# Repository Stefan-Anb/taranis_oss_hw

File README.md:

# Taranis Pcb

BMS PCB for Taranis Project
Kicad files
PCB Layout is not finished yet. Schematics are proven from a proprietary project.

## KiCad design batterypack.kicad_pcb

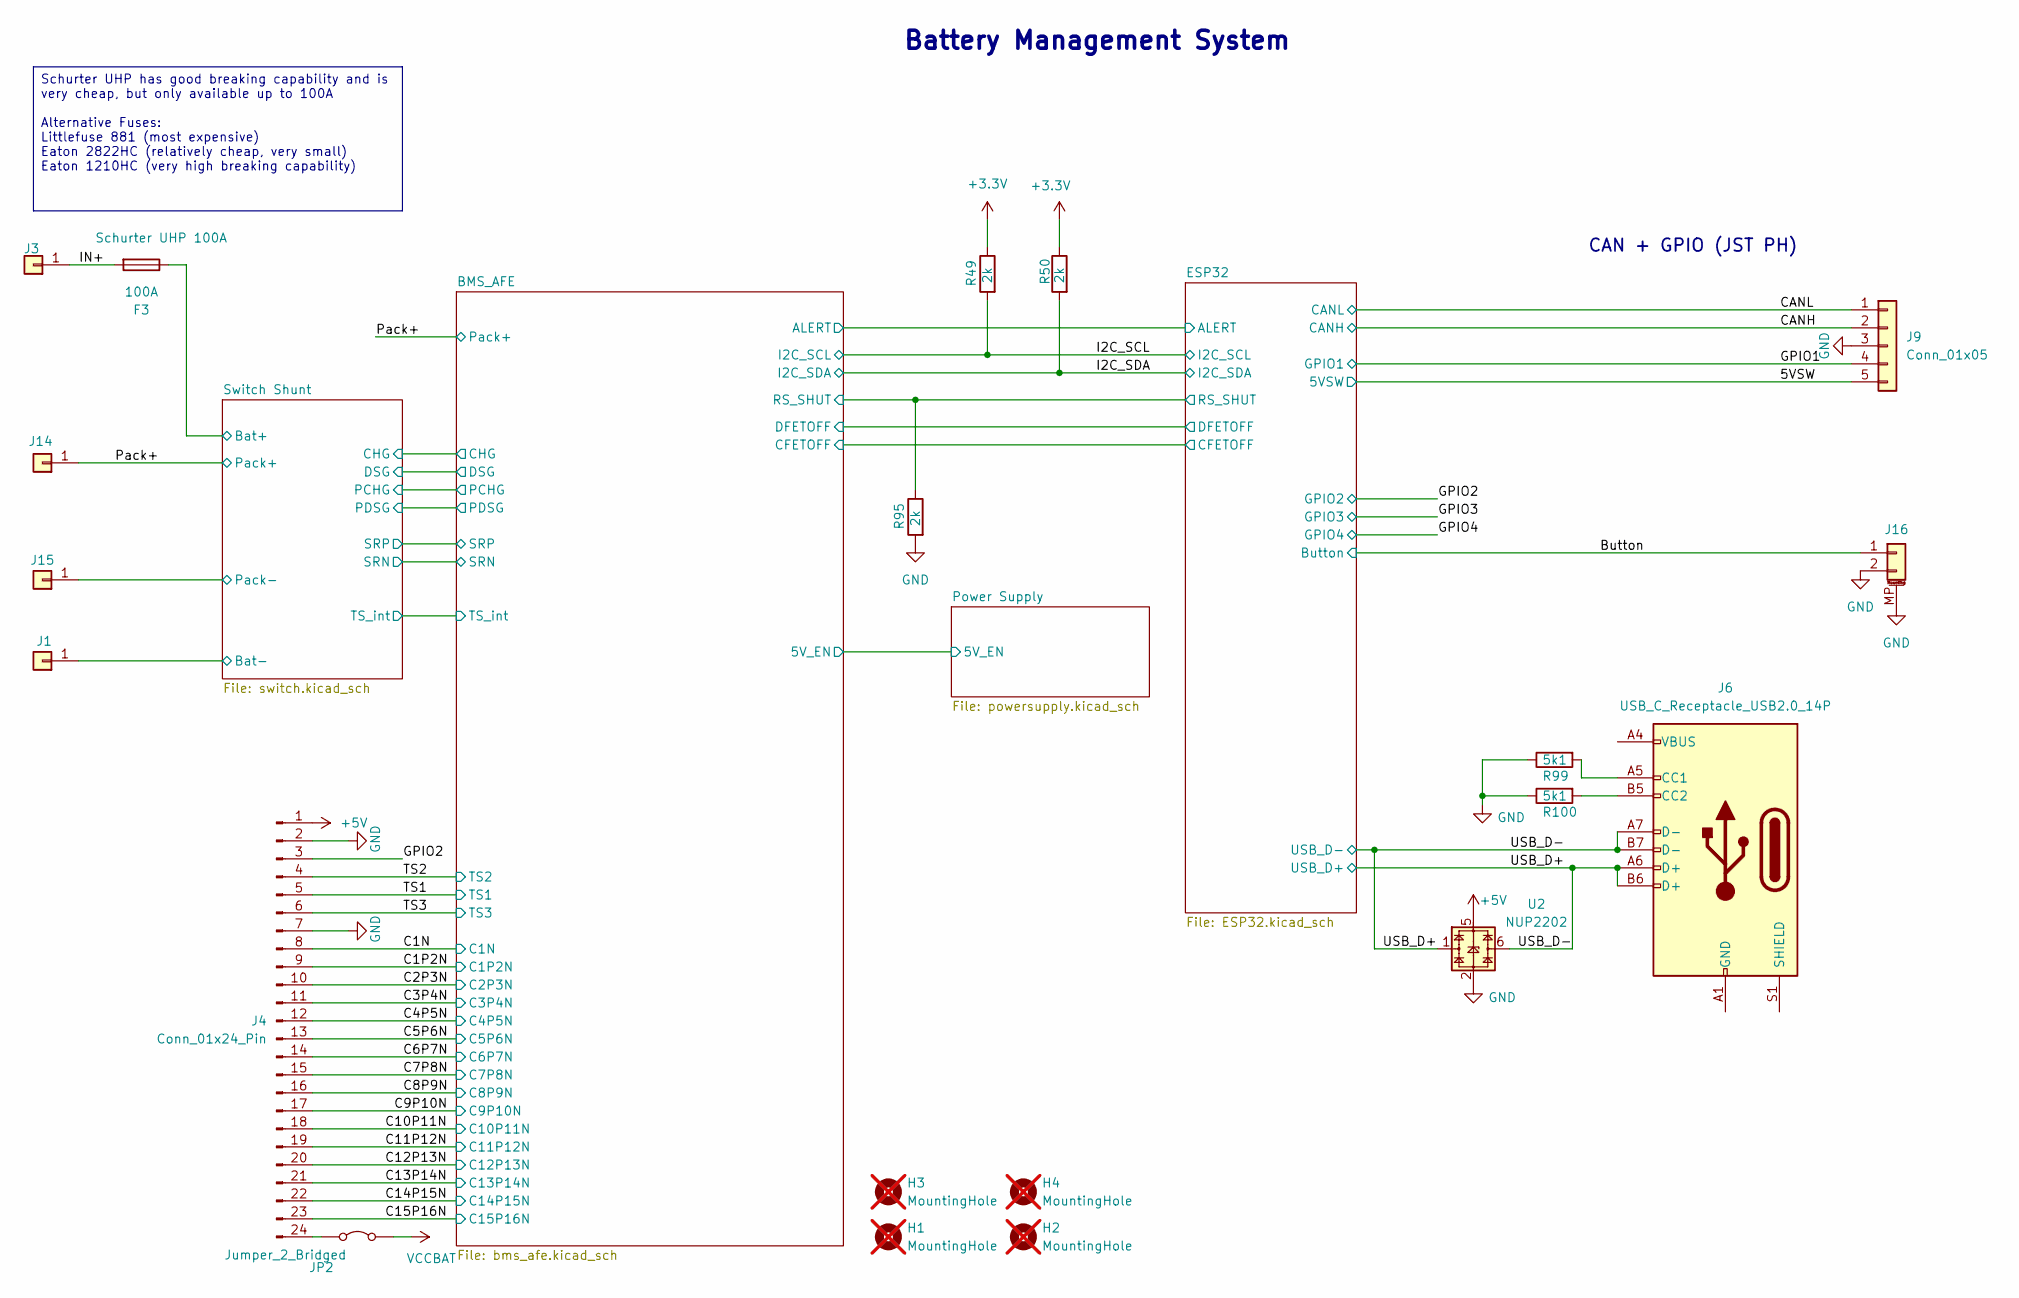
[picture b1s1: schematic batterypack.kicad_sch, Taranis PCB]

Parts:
F3: 100A; Shurter_UHP; MPN C20110673
H1, H2, H3, H4: MountingHole; MountingHole_3.2mm_M3; not fitted
J1, J3: Conn_01x01; Wuerth_REDCUBE-THR_WP-THRBU_74650094_THR; MPN C9900208421
J4: Conn_01x24_Pin
J6: USB_C_Receptacle_USB2.0_14P
J9: Conn_01x05
J14, J15: Conn_01x01; Wuerth_REDCUBE-THR_WP-THRBU_74650094_THR; MPN C25168763
J16: Conn_01x02; JST_PH_S2B-PH-K_1x02_P2.00mm_Horizontal; MPN C160352
JP2: Jumper_2_Bridged; SolderJumper-2_P1.3mm_Bridged_RoundedPad1.0x1.5mm
R49, R50, R95: 2k; R_0402_1005Metric; MPN C4109
R99, R100: 5k1; R_0402_1005Metric; MPN C25905
U2: NUP2202; SOT-363_SC-70-6; MPN C4355033

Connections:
+3.3V: R49.1, R50.1; also elsewhere on the board
+5V: J4.1, J4.5, U2.5; also elsewhere on the board
/BMS_AFE/RS_SHUT: R95.1; also elsewhere on the board
/Button: J16.1; also elsewhere on the board
/C1N: J4.12; also elsewhere on the board
/C1P2N: J4.13; also elsewhere on the board
/C2P3N: J4.14; also elsewhere on the board
/C3P4N: J4.15; also elsewhere on the board
/C4P5N: J4.16; also elsewhere on the board
/C5P6N: J4.17; also elsewhere on the board
/C6P7N: J4.18; also elsewhere on the board
/C7P8N: J4.19; also elsewhere on the board
/C8P9N: J4.20; also elsewhere on the board
/C9P10N: J4.21; also elsewhere on the board
/C10P11N: J4.22; also elsewhere on the board
/C11P12N: J4.23; also elsewhere on the board
/C13P14N: J4.25; also elsewhere on the board
/C14P15N: J4.26; also elsewhere on the board
/C15P16N: J4.27; also elsewhere on the board
/I2C_SCL: R49.2; also elsewhere on the board
/I2C_SDA: R50.2; also elsewhere on the board
/IN+: F3.2, J3.1
/Pack+: J14.1; also elsewhere on the board
/Switch Shunt/Bat+: F3.1; also elsewhere on the board
/Switch Shunt/Bat-: J1.1; also elsewhere on the board
/Switch Shunt/Pack-: J15.1; also elsewhere on the board
/TS1: J4.9; also elsewhere on the board
/TS2: J4.8; also elsewhere on the board
/TS3: J4.10; also elsewhere on the board
/USB_D+: J6.A6 (D+), J6.A7 (D-), J6.B6 (D+), J6.B7 (D-), U2.1, U2.6; also elsewhere on the board
unnamed: J6.A5 (CC1), R99.2
unnamed: J6.B5 (CC2), R100.2
unnamed: J6.A1 (GND), J6.A12 (GND), J6.B1 (GND), J6.B12 (GND)
unnamed: J6.A4 (VBUS), J6.A9 (VBUS), J6.B4 (VBUS), J6.B9 (VBUS)
VCCBAT: JP2.2 (B); also elsewhere on the board

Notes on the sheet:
Battery Management System
CAN + GPIO (JST PH)
Schurter UHP has good breaking capability and is very cheap, but only available up to 100A Alternative Fuses: Littlefuse 881 (most expensive) Eaton 2822HC (relatively cheap, very small) Eaton 1210HC (very high breaking capability)

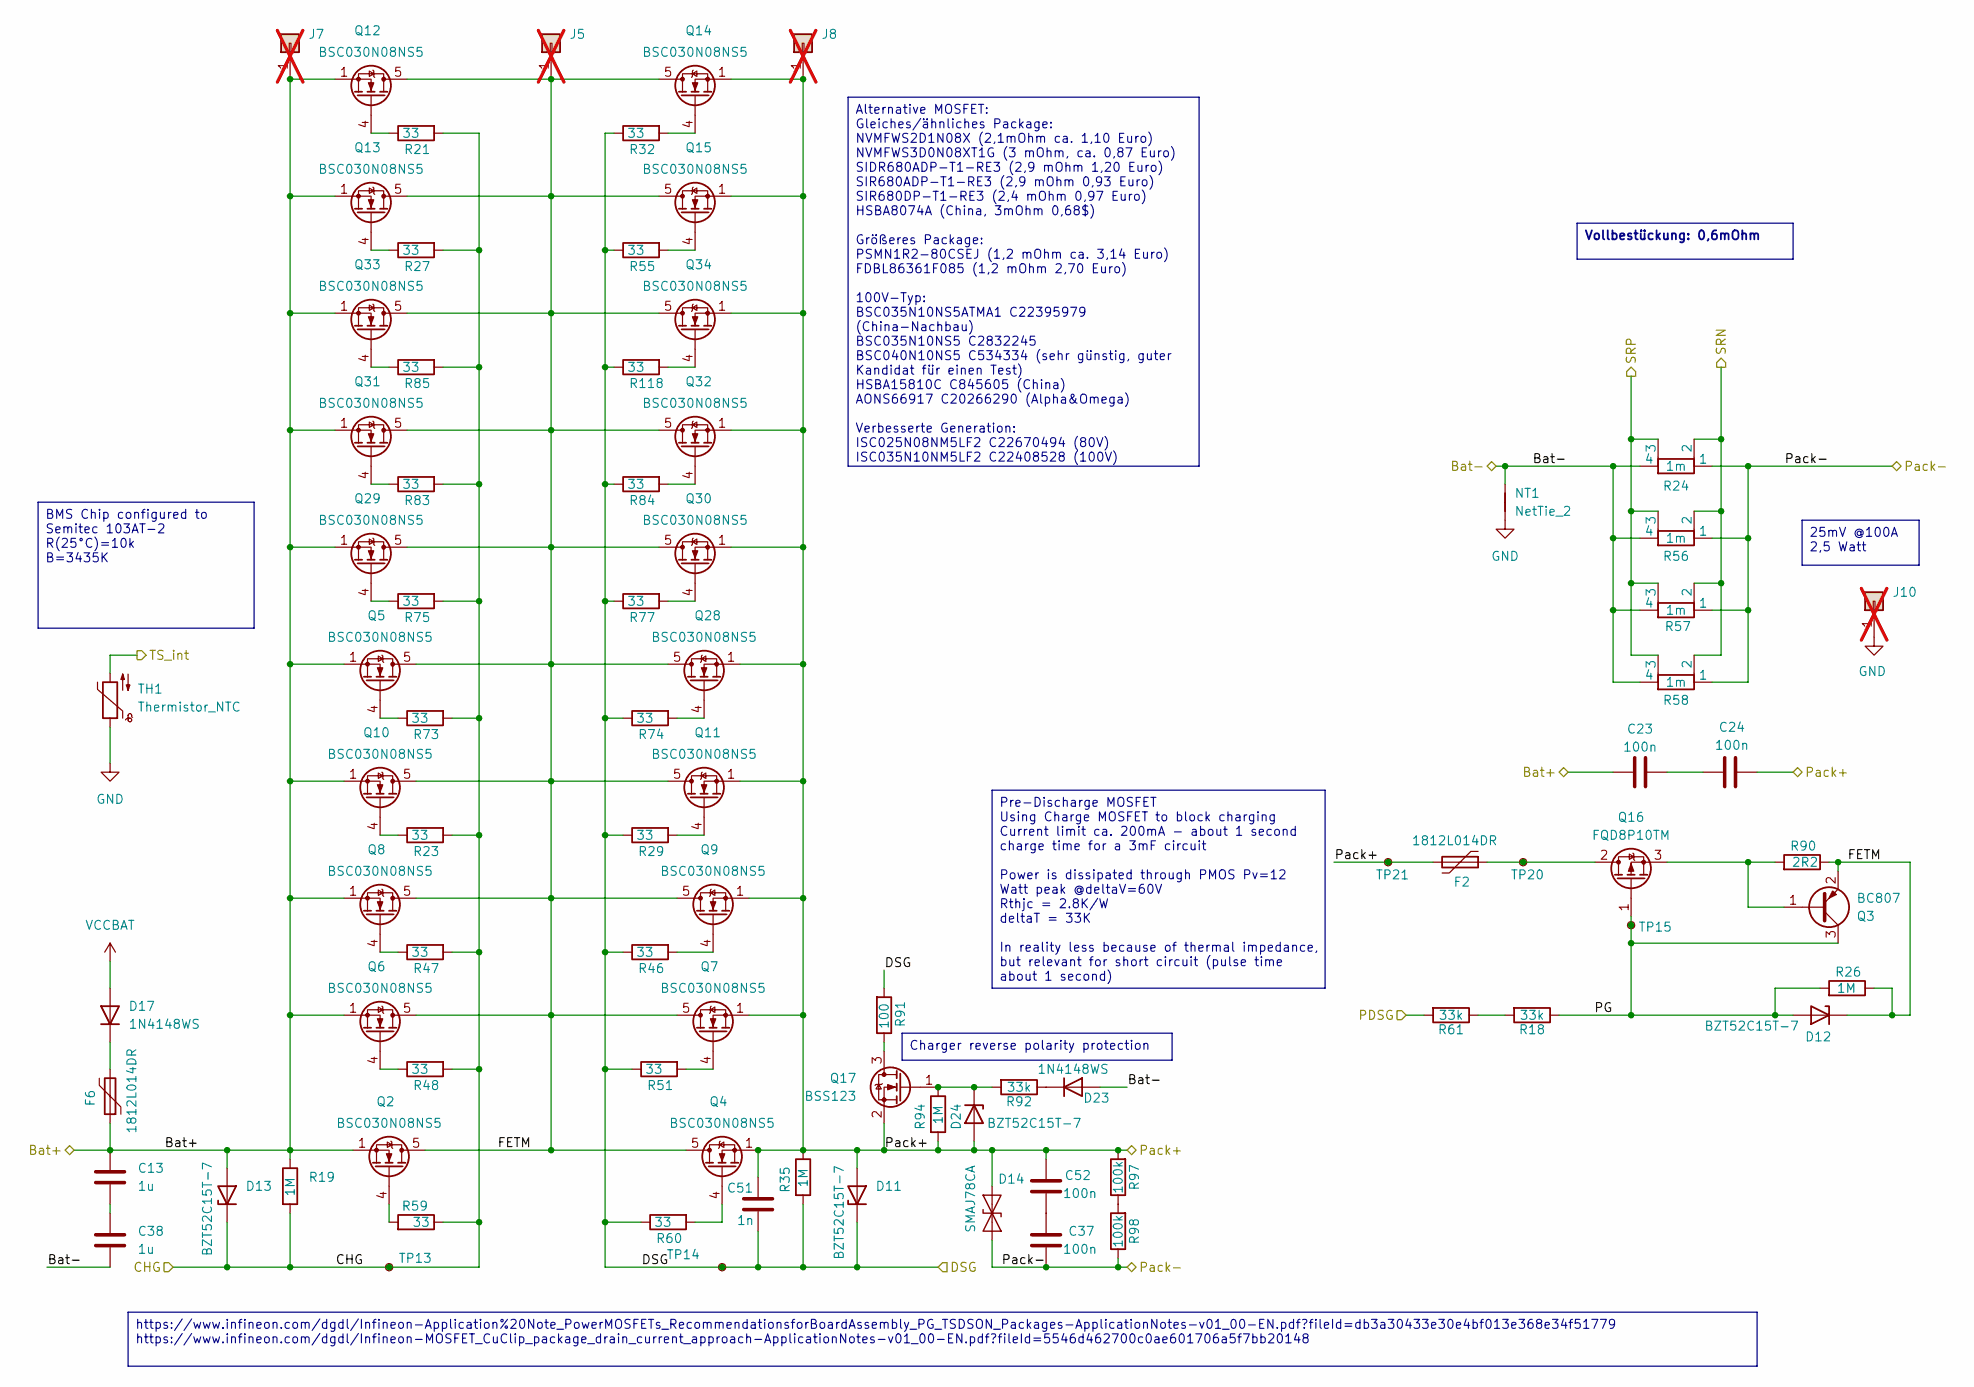
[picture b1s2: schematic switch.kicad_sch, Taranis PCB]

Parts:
C13, C38: 1u; C_0805_2012Metric; MPN C5370002
C23, C24, C37, C52: 100n; C_0805_2012Metric; MPN C28233
C51: 1n; C_0402_1005Metric; MPN C1523
D11, D12, D13, D24: BZT52C15T-7; D_SOD-523; MPN C460787
D14: SMAJ78CA; D_SMA; MPN C3720737
D17, D23: 1N4148WS; D_SOD-323; MPN C2128
F2, F6: 1812L014DR; R_1812_4532Metric; MPN C151166
J5: Conn_01x01; TestPoint_Pad_D1.5mm; not fitted
J7, J8, J10: Conn_01x01; PinHeader_1x01_P2.54mm_Vertical; not fitted
NT1: NetTie_2; NetTie-2_SMD_Pad0.5mm
Q2, Q4, Q5, Q6, Q7, Q8, Q9, Q10, Q11, Q12, Q13, Q14, Q15, Q28, Q29, Q30, Q31, Q32, Q33, Q34: BSC030N08NS5; TDSON-8-1; MPN C501507
Q3: BC807; SOT-23; MPN C57316
Q16: FQD8P10TM; TO-252-2; MPN C241842
Q17: BSS123; SOT-23; MPN C78755
R18, R61, R92: 33k; R_0402_1005Metric; MPN C25779
R19, R26, R35, R94: 1M; R_0402_1005Metric; MPN C26083
R21, R23, R27, R29, R32, R46, R47, R48, R51, R55, R59, R60, R73, R74, R75, R77, R83, R84, R85, R118: 33; R_0402_1005Metric; MPN C25105
R24, R56, R57, R58: 1m; Shunt; MPN C326570
R90: 2R2; R_1206_3216Metric; MPN C17947
R91: 100; R_0402_1005Metric; MPN C25076
R97, R98: 100k; R_0402_1005Metric; MPN C25741
TH1: Thermistor_NTC; R_0603_1608Metric; MPN C525660
TP13, TP14, TP15: TestPoint_Small; TestPoint_Pad_D1.0mm
TP20, TP21: TestPoint_Small; TestPoint_THTPad_D1.5mm_Drill0.7mm

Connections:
/BMS_AFE/PDSG: R61.2; also elsewhere on the board
/BMS_AFE/SRN: R24.2, R56.2, R57.2, R58.2; also elsewhere on the board
/BMS_AFE/SRP: R24.3, R56.3, R57.3, R58.3; also elsewhere on the board
/BMS_AFE/TS_int: TH1.2; also elsewhere on the board
/Pack+: C24.2, C51.2, C52.2, D11.2 (A), D14.1 (A1), D24.2 (A), F2.2, J8.1, Q4.1 (S), Q4.2 (S), Q4.3 (S), Q7.1 (S), Q7.2 (S), Q7.3 (S), Q9.1 (S), Q9.2 (S), Q9.3 (S), Q11.1 (S), Q11.2 (S), Q11.3 (S), Q14.1 (S), Q14.2 (S), Q14.3 (S), Q15.1 (S), Q15.2 (S), Q15.3 (S), Q17.2 (S), Q28.1 (S), Q28.2 (S), Q28.3 (S), Q30.1 (S), Q30.2 (S), Q30.3 (S), Q32.1 (S), Q32.2 (S), Q32.3 (S), Q34.1 (S), Q34.2 (S), Q34.3 (S), R35.1, R94.2, R97.2, TP21.1; also elsewhere on the board
/Switch Shunt/Bat+: C13.2, C23.1, D13.2 (A), F6.1, J7.1, Q2.1 (S), Q2.2 (S), Q2.3 (S), Q5.1 (S), Q5.2 (S), Q5.3 (S), Q6.1 (S), Q6.2 (S), Q6.3 (S), Q8.1 (S), Q8.2 (S), Q8.3 (S), Q10.1 (S), Q10.2 (S), Q10.3 (S), Q12.1 (S), Q12.2 (S), Q12.3 (S), Q13.1 (S), Q13.2 (S), Q13.3 (S), Q29.1 (S), Q29.2 (S), Q29.3 (S), Q31.1 (S), Q31.2 (S), Q31.3 (S), Q33.1 (S), Q33.2 (S), Q33.3 (S), R19.1; also elsewhere on the board
/Switch Shunt/Bat-: C38.1, D23.2 (A), NT1.2, R24.4, R56.4, R57.4, R58.4; also elsewhere on the board
/Switch Shunt/CHG: D13.1 (K), R19.2, R21.2, R23.2, R27.2, R47.2, R48.2, R59.1, R73.2, R75.2, R83.2, R85.2, TP13.1; also elsewhere on the board
/Switch Shunt/DSG: C51.1, D11.1 (K), R29.1, R32.1, R35.2, R46.1, R51.1, R55.1, R60.1, R74.1, R77.1, R84.1, R91.2, R118.1, TP14.1; also elsewhere on the board
/Switch Shunt/FETM: D12.1 (K), J5.1, Q2.5 (D), Q3.2 (E), Q4.5 (D), Q5.5 (D), Q6.5 (D), Q7.5 (D), Q8.5 (D), Q9.5 (D), Q10.5 (D), Q11.5 (D), Q12.5 (D), Q13.5 (D), Q14.5 (D), Q15.5 (D), Q28.5 (D), Q29.5 (D), Q30.5 (D), Q31.5 (D), Q32.5 (D), Q33.5 (D), Q34.5 (D), R26.1, R90.1
/Switch Shunt/PG: D12.2 (A), Q3.3 (C), Q16.1 (G), R18.1, R26.2, TP15.1
/Switch Shunt/Pack-: C37.1, D14.2 (A2), R24.1, R56.1, R57.1, R58.1, R98.1; also elsewhere on the board
unnamed: C13.1, C38.2
unnamed: C23.2, C24.1
unnamed: C37.2, C52.1
unnamed: D17.1 (K), F6.2
unnamed: D23.1 (K), R92.1
unnamed: D24.1 (K), Q17.1 (G), R92.2, R94.1
unnamed: Q2.4 (G), R59.2
unnamed: Q4.4 (G), R60.2
unnamed: Q5.4 (G), R73.1
unnamed: Q6.4 (G), R48.1
unnamed: Q7.4 (G), R51.2
unnamed: Q8.4 (G), R47.1
unnamed: Q9.4 (G), R46.2
unnamed: Q10.4 (G), R23.1
unnamed: Q11.4 (G), R29.2
unnamed: Q12.4 (G), R21.1
unnamed: Q13.4 (G), R27.1
unnamed: Q14.4 (G), R32.2
unnamed: Q15.4 (G), R55.2
unnamed: F2.1, Q16.2 (D), TP20.1
unnamed: Q3.1 (B), Q16.3 (S), R90.2
unnamed: Q17.3 (D), R91.1
unnamed: Q28.4 (G), R74.2
unnamed: Q29.4 (G), R75.1
unnamed: Q30.4 (G), R77.2
unnamed: Q31.4 (G), R83.1
unnamed: Q32.4 (G), R84.2
unnamed: Q33.4 (G), R85.1
unnamed: Q34.4 (G), R118.2
unnamed: R18.2, R61.1
unnamed: R97.1, R98.2
VCCBAT: D17.2 (A); also elsewhere on the board

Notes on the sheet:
25mV @100A 2,5 Watt
Vollbestückung: 0,6mOhm
https://www.infineon.com/dgdl/Infineon-Application%20Note_PowerMOSFETs_RecommendationsforBoardAssembly_PG_TSDSON_Packages-ApplicationNotes-v01_00-EN.pdf?fileId=db3a30433e30e4bf013e368e34f51779 https://www.infineon.com/dgdl/Infineon-MOSFET_CuClip_package_drain_current_approach-ApplicationNotes-v01_0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
Alternative MOSFET: Gleiches/ähnliches Package: NVMFWS2D1N08X (2,1mOhm ca. 1,10 Euro) NVMFWS3D0N08XT1G (3 mOhm, ca. 0,87 Euro) SIDR680ADP-T1-RE3 (2,9 mOhm 1,20 Euro) SIR680ADP-T1-RE3 (2,9 mOhm 0,93 Euro) SIR680DP-T1-RE3 (2,4 mOhm 0,97 Euro) HSBA8074A (China, 3mOhm 0,68$) Größeres Package: PSMN1R2-8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
Pre-Discharge MOSFET Using Charge MOSFET to block charging Current limit ca. 200mA - about 1 second charge time for a 3mF circuit Power is dissipated through PMOS Pv=12 Watt peak @deltaV=60V Rthjc = 2.8K/W deltaT = 33K In reality less because of thermal impedance, but relevant for short circuit (pu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
Charger reverse polarity protection
BMS Chip configured to Semitec 103AT-2 R(25°C)=10k B=3435K

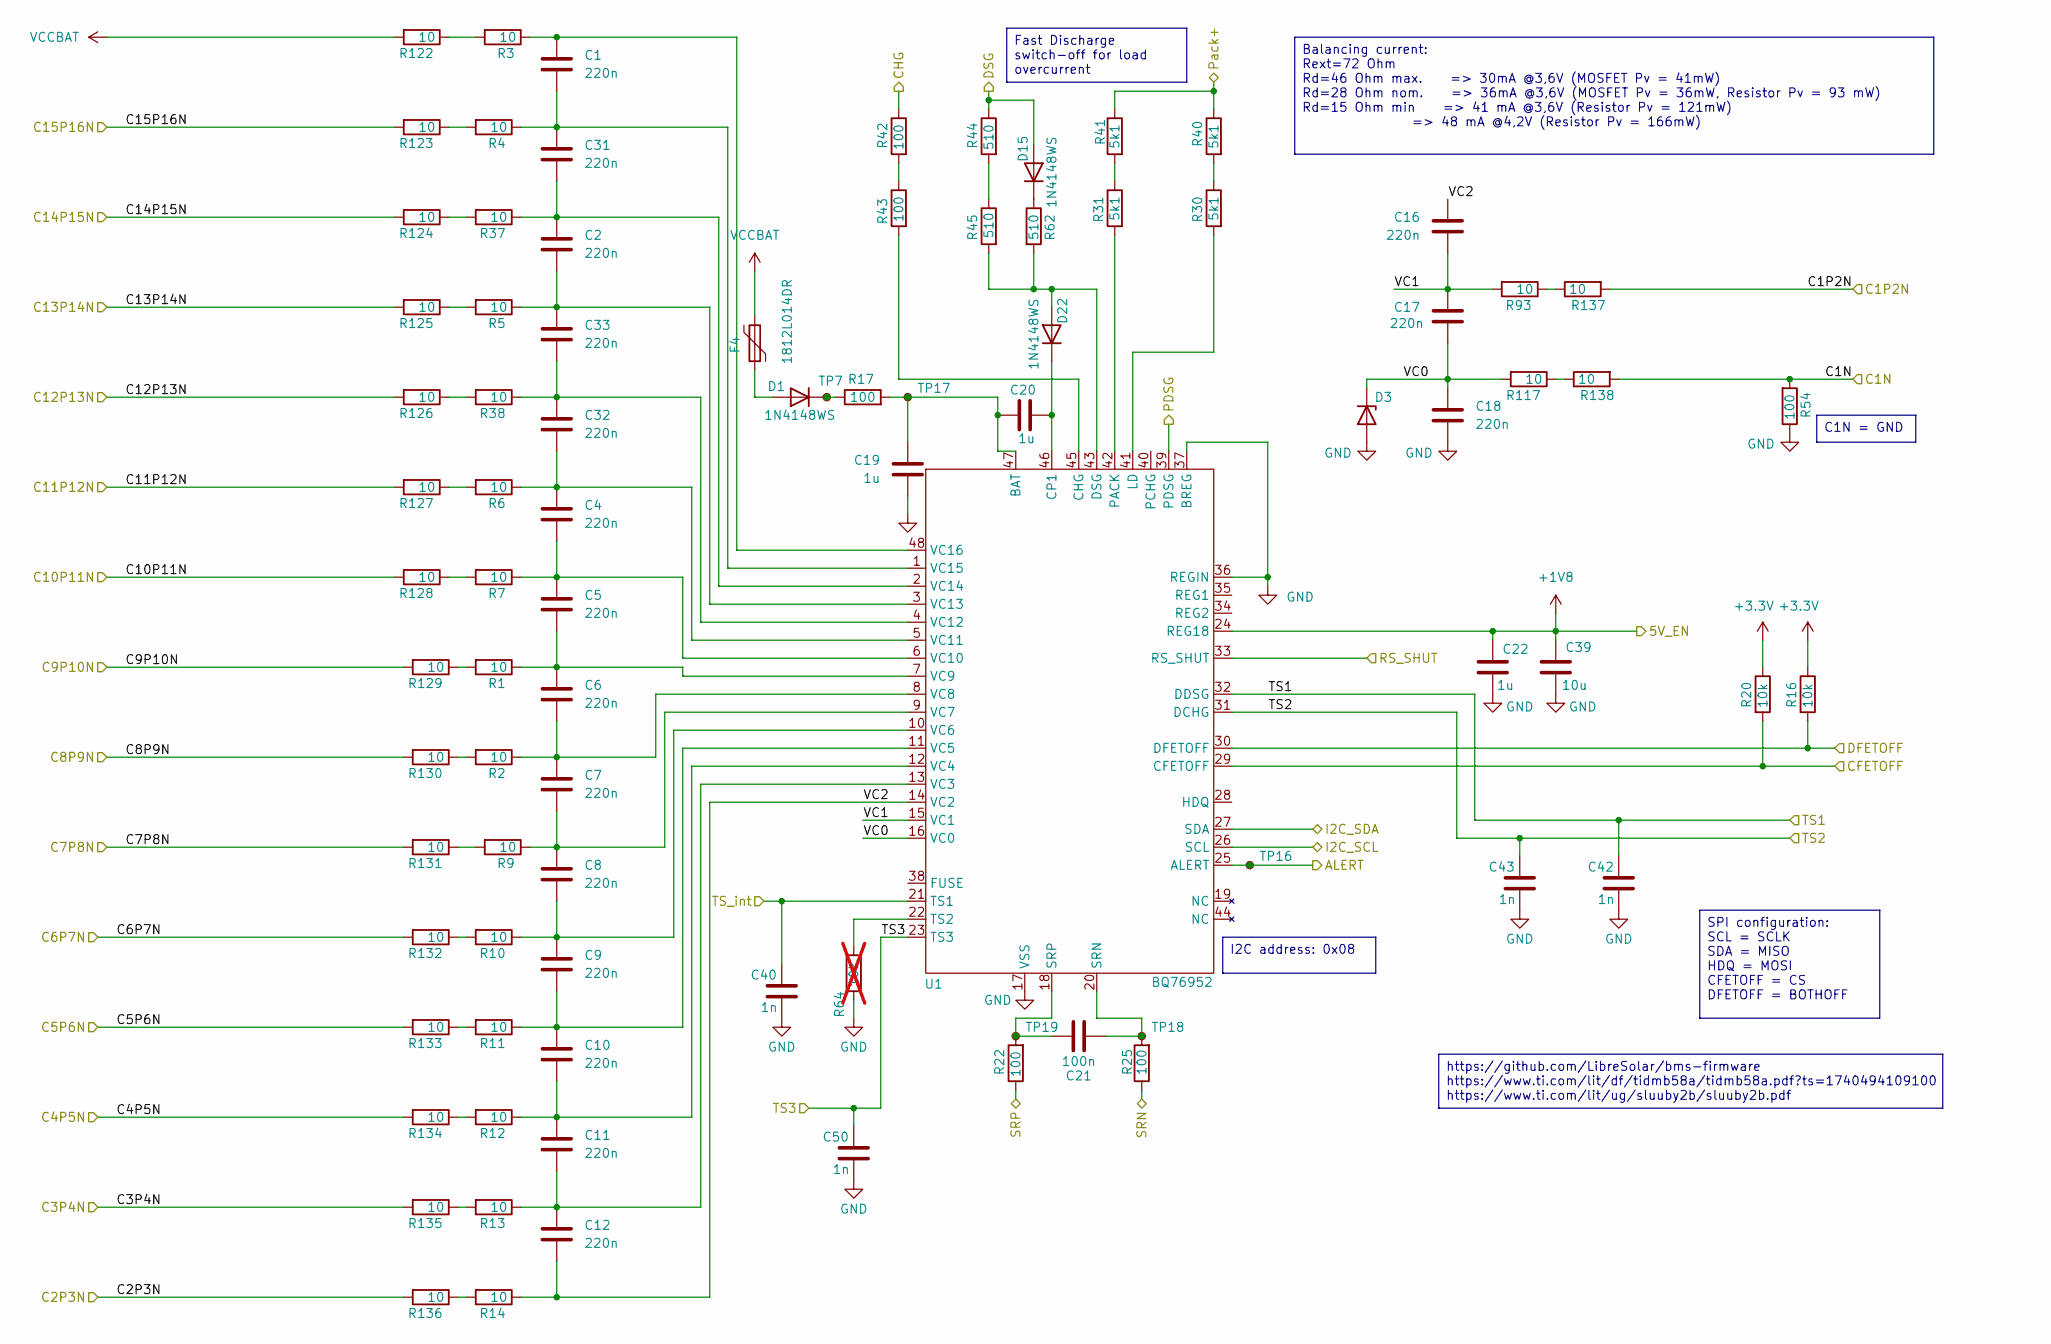
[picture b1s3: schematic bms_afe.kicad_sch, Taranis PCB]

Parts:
C1, C2, C4, C5, C6, C7, C8, C9, C10, C11, C12, C16, C17, C18, C31, C32, C33: 220n; C_0402_1005Metric; MPN C16772
C19, C20: 1u; C_1206_3216Metric; MPN C13832
C21: 100n; C_0402_1005Metric; MPN C307331
C22: 1u; C_0402_1005Metric; MPN C52923
C39: 10u; C_0402_1005Metric; MPN C15525
C40, C42, C43, C50: 1n; C_0402_1005Metric; MPN C1523
D1, D15, D22: 1N4148WS; D_SOD-323; MPN C2128
D3: PESD3V3U1UA,115; D_SOD-323; MPN C403915
F4: 1812L014DR; R_1812_4532Metric; MPN C151166
R1, R2, R3, R4, R5, R6, R7, R9, R10, R11, R12, R13, R14, R37, R38, R93, R117, R122, R123, R124, R125, R126, R127, R128, R129, R130, R131, R132, R133, R134, R135, R136, R137, R138: 10; R_0603_1608Metric; MPN C22859
R16, R20: 10k; R_0402_1005Metric; MPN C25744
R17, R22, R25, R42, R43, R54: 100; R_0402_1005Metric; MPN C25076
R30, R31, R40, R41: 5k1; R_0402_1005Metric; MPN C25905
R44, R45, R62: 510; R_0603_1608Metric; MPN C23193
R64: 10k; R_0402_1005Metric; MPN C25744; not fitted
TP7, TP16, TP17, TP18, TP19: TestPoint_Small; TestPoint_Pad_D1.0mm
U1: BQ76952; TQFP-48_7x7mm_P0.5mm; MPN C2862742

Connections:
+1V8: C22.1, C39.2, U1.24 (REG18); also elsewhere on the board
+3.3V: R16.1, R20.1; also elsewhere on the board
/BMS_AFE/ALERT: TP16.1, U1.25 (ALERT); also elsewhere on the board
/BMS_AFE/CFETOFF: R20.2, U1.29 (CFETOFF); also elsewhere on the board
/BMS_AFE/DFETOFF: R16.2, U1.30 (DFETOFF); also elsewhere on the board
/BMS_AFE/PDSG: U1.39 (PDSG); also elsewhere on the board
/BMS_AFE/RS_SHUT: U1.33 (RS_SHUT); also elsewhere on the board
/BMS_AFE/SRN: R25.1; also elsewhere on the board
/BMS_AFE/SRP: R22.1; also elsewhere on the board
/BMS_AFE/TS_int: C40.2, U1.21 (TS1); also elsewhere on the board
/BMS_AFE/VC0: C17.2, C18.1, D3.1 (K), R117.2, U1.16 (VC0)
/BMS_AFE/VC1: C16.2, C17.1, R93.2, U1.15 (VC1)
/BMS_AFE/VC2: C12.2, C16.1, R14.1, U1.14 (VC2)
/C1N: R54.2, R138.2; also elsewhere on the board
/C1P2N: R137.2; also elsewhere on the board
/C2P3N: R136.2; also elsewhere on the board
/C3P4N: R135.2; also elsewhere on the board
/C4P5N: R134.2; also elsewhere on the board
/C5P6N: R133.2; also elsewhere on the board
/C6P7N: R132.2; also elsewhere on the board
/C7P8N: R131.2; also elsewhere on the board
/C8P9N: R130.2; also elsewhere on the board
/C9P10N: R129.2; also elsewhere on the board
/C10P11N: R128.2; also elsewhere on the board
/C11P12N: R127.2; also elsewhere on the board
/C13P14N: R125.2; also elsewhere on the board
/C14P15N: R124.2; also elsewhere on the board
/C15P16N: R123.2; also elsewhere on the board
/I2C_SCL: U1.26 (SCL); also elsewhere on the board
/I2C_SDA: U1.27 (SDA); also elsewhere on the board
/Pack+: R40.1, R41.1; also elsewhere on the board
/Switch Shunt/CHG: R42.1; also elsewhere on the board
/Switch Shunt/DSG: D15.2 (A), R44.1; also elsewhere on the board
/TS1: C42.2, U1.32 (DDSG); also elsewhere on the board
/TS2: C43.2, U1.31 (DCHG); also elsewhere on the board
/TS3: C50.2, U1.23 (TS3); also elsewhere on the board
unnamed: D1.2 (A), F4.1
unnamed: D1.1 (K), R17.1, TP7.1
unnamed: D15.1 (K), R62.1
unnamed: D22.2 (A), R45.2, R62.2, U1.43 (DSG)
unnamed: C20.2, D22.1 (K), U1.46 (CP1)
unnamed: R1.2, R129.1
unnamed: R10.2, R132.1
unnamed: R11.2, R133.1
unnamed: R12.2, R134.1
unnamed: R13.2, R135.1
unnamed: R30.1, R40.2
unnamed: R31.1, R41.2
unnamed: R42.2, R43.1
unnamed: R44.2, R45.1
unnamed: R117.1, R138.1
unnamed: R3.2, R122.1
unnamed: R4.2, R123.1
unnamed: R37.2, R124.1
unnamed: R5.2, R125.1
unnamed: R38.2, R126.1
unnamed: R6.2, R127.1
unnamed: R7.2, R128.1
unnamed: R2.2, R130.1
unnamed: R9.2, R131.1
unnamed: R14.2, R136.1
unnamed: R93.1, R137.1
unnamed: C19.1, C20.1, R17.2, TP17.1, U1.47 (BAT)
unnamed: R43.2, U1.45 (CHG)
unnamed: R30.2, U1.41 (LD)
unnamed: R31.2, U1.42 (PACK)
unnamed: C21.2, R25.2, TP18.1, U1.20 (SRN)
unnamed: C21.1, R22.2, TP19.1, U1.18 (SRP)
unnamed: R64.1, U1.22 (TS2)
unnamed: C11.2, C12.1, R13.1, U1.13 (VC3)
unnamed: C10.2, C11.1, R12.1, U1.12 (VC4)
unnamed: C9.2, C10.1, R11.1, U1.11 (VC5)
unnamed: C8.2, C9.1, R10.1, U1.10 (VC6)
unnamed: C7.2, C8.1, R9.1, U1.9 (VC7)
unnamed: C6.2, C7.1, R2.1, U1.8 (VC8)
unnamed: C5.2, C6.1, R1.1, U1.7 (VC9)
unnamed: C4.2, C5.1, R7.1, U1.6 (VC10)
unnamed: C4.1, C32.2, R6.1, U1.5 (VC11)
unnamed: C32.1, C33.2, R38.1, U1.4 (VC12)
unnamed: C2.2, C33.1, R5.1, U1.3 (VC13)
unnamed: C2.1, C31.2, R37.1, U1.2 (VC14)
unnamed: C1.2, C31.1, R4.1, U1.1 (VC15)
unnamed: C1.1, R3.1, U1.48 (VC16)
VCCBAT: F4.2, R122.2; also elsewhere on the board

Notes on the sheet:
SPI configuration: SCL = SCLK SDA = MISO HDQ = MOSI CFETOFF = CS DFETOFF = BOTHOFF
I2C address: 0x08
C1N = GND
https://github.com/LibreSolar/bms-firmware https://www.ti.com/lit/df/tidmb58a/tidmb58a.pdf?ts=1740494109100 https://www.ti.com/lit/ug/sluuby2b/sluuby2b.pdf
Fast Discharge switch-off for load overcurrent
Balancing current: Rext=72 Ohm Rd=46 Ohm max. => 30mA @3,6V (MOSFET Pv = 41mW) Rd=28 Ohm nom. => 36mA @3,6V (MOSFET Pv = 36mW, Resistor Pv = 93 mW) Rd=15 Ohm min => 41 mA @3,6V (Resistor Pv = 121mW) => 48 mA @4,2V (Resistor Pv = 166mW)

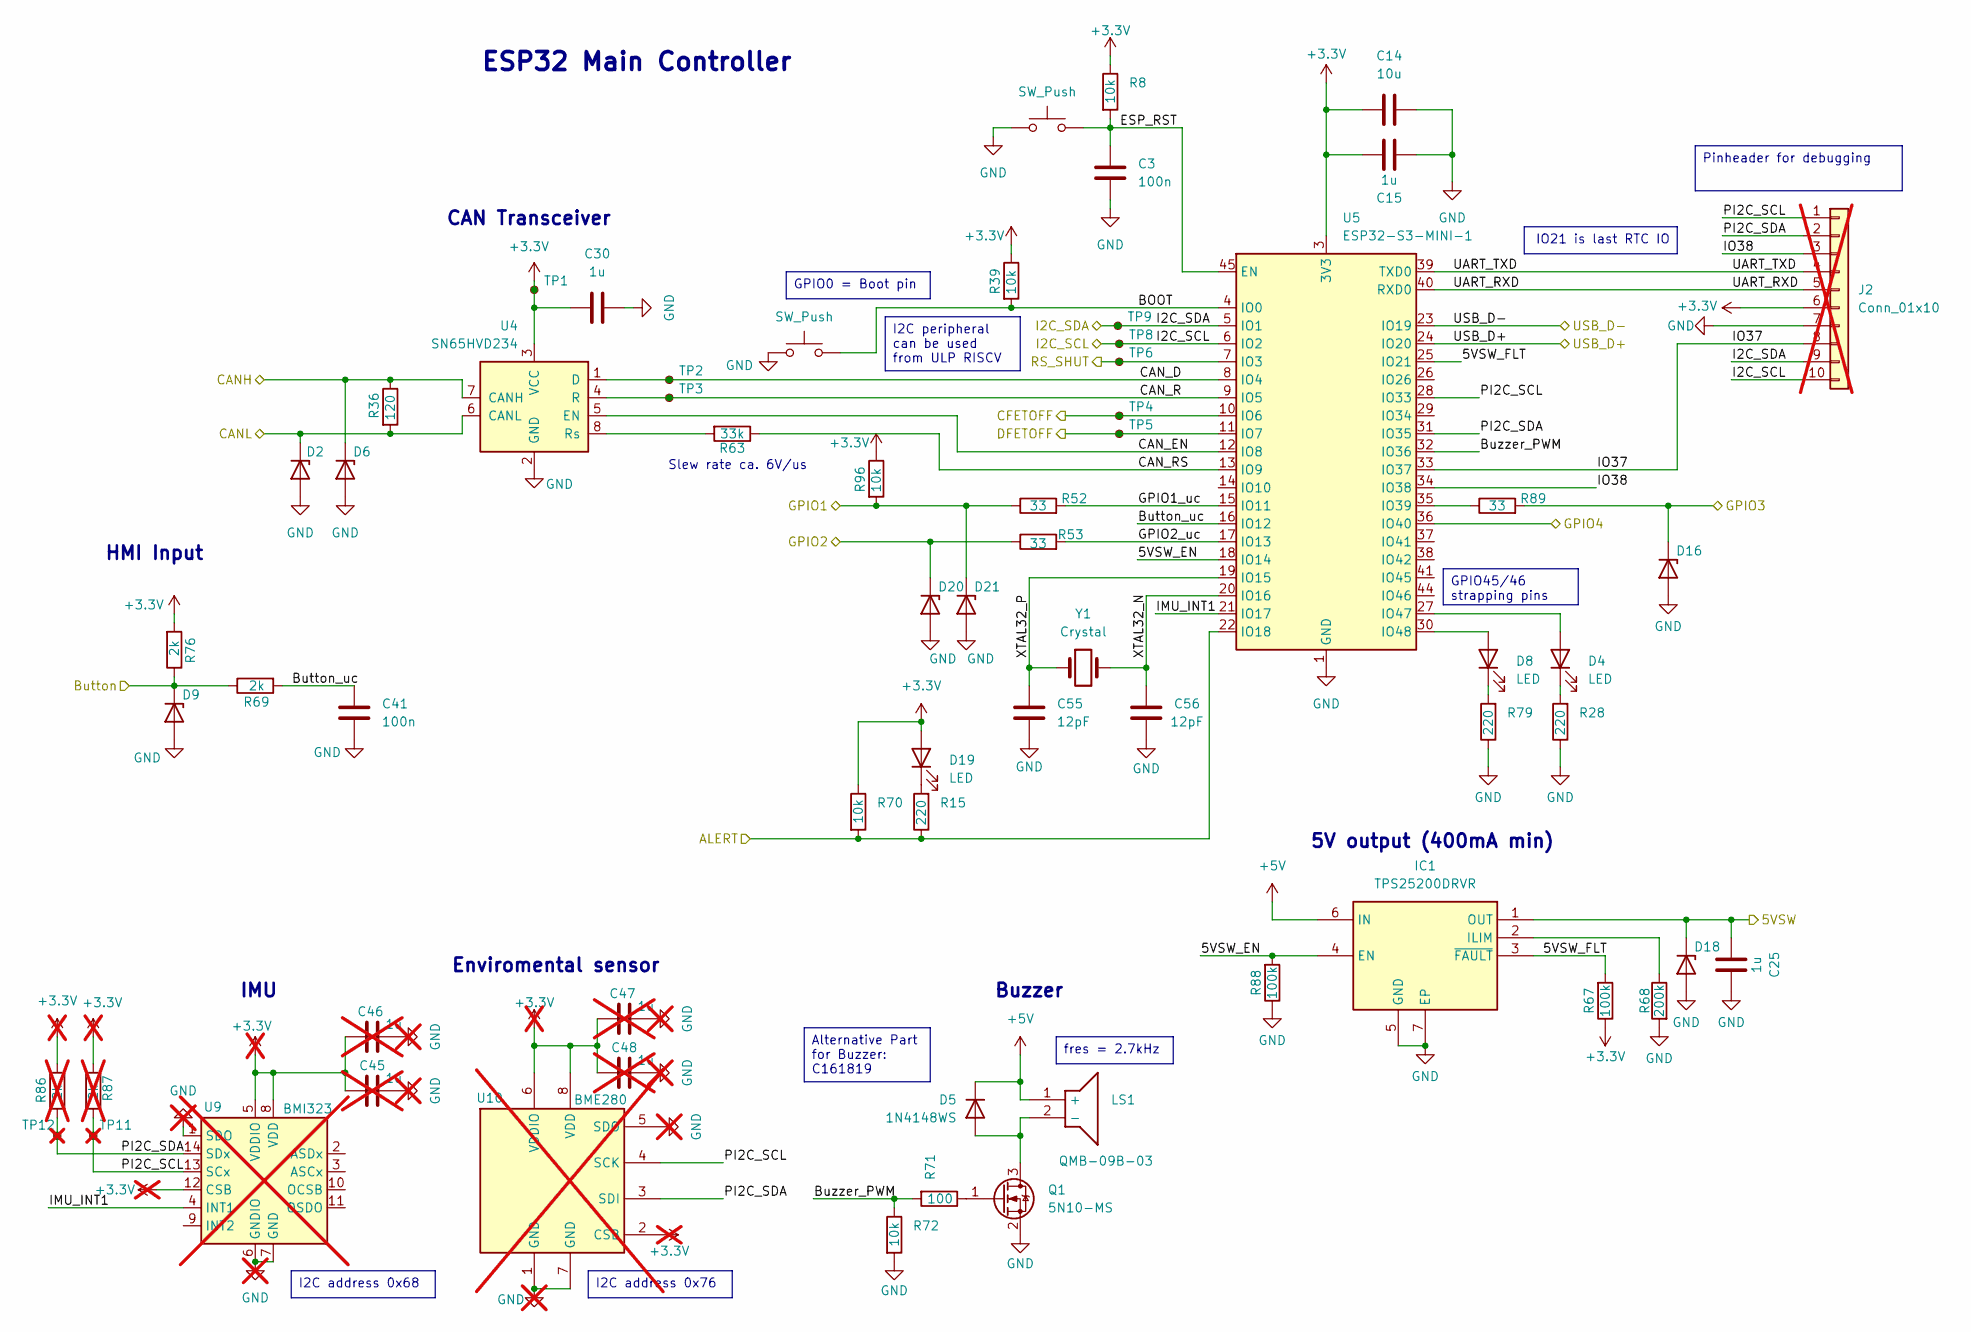
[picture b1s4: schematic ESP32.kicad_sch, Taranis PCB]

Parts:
C3, C41: 100n; C_0402_1005Metric; MPN C307331
C14: 10u; C_0402_1005Metric; MPN C15525
C15, C25, C30: 1u; C_0402_1005Metric; MPN C52923
C45, C46, C47, C48: 1u; C_0402_1005Metric; MPN C52923; not fitted
C55, C56: 12pF; C_0402_1005Metric; MPN C1547
D2, D6, D18: SP4021-01FTG; D_SOD-323; MPN C316004
D4, D8, D19: LED; LED_0603_1608Metric; MPN C2286
D5: 1N4148WS; D_SOD-323; MPN C2128
D9, D16, D20, D21: PESD3V3U1UA,115; D_SOD-323; MPN C403915
IC1: TPS25200DRVR; SON65P200X200X80-7N; Manufacturer_Part_Number TPS25200DRVR; Mouser Part Number 595-TPS25200DRVR
J2: Conn_01x10; PinHeader_1x10_P2.54mm_Vertical; not fitted
LS1: QMB-09B-03; QMB09B03; Manufacturer_Part_Number QMB-09B-03
Q1: 5N10-MS; SOT-23; MPN C5140036
R8, R39, R70, R72, R96: 10k; R_0402_1005Metric; MPN C25744
R15, R28, R79: 220; R_0402_1005Metric; MPN C25091
R36: 120; R_1206_3216Metric; MPN C17909
R52, R53, R89: 33; R_0402_1005Metric; MPN C25105
R63: 33k; R_0402_1005Metric; MPN C25779
R67, R88: 100k; R_0402_1005Metric; MPN C25741
R68: 200k; R_0402_1005Metric; MPN C25764
R69, R76: 2k; R_0402_1005Metric; MPN C4109
R71: 100; R_0402_1005Metric; MPN C25076
R86, R87: 2k; R_0402_1005Metric; MPN C4109; not fitted
SW1, SW2: SW_Push; SW_Push_1P1T_XKB_TS-1187A; MPN C318884
TP1, TP2, TP3, TP4, TP5, TP6, TP8, TP9: TestPoint_Small; TestPoint_Pad_D1.0mm
TP11, TP12: TestPoint_Small; TestPoint_Pad_D1.0mm; not fitted
U4: SN65HVD234; SOIC-8_3.9x4.9mm_P1.27mm; MPN C99818
U5: ESP32-S3-MINI-1; ESP32-S2-MINI-1; MPN C2913206
U9: BMI323; Bosch_LGA-14_3x2.5mm_P0.5mm; MPN C5368700; not fitted
U10: BME280; Bosch_LGA-8_2.5x2.5mm_P0.65mm_ClockwisePinNumbering; MPN C92489; not fitted
Y1: Crystal; Crystal_SMD_3215-2Pin_3.2x1.5mm; MPN C32346

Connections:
+3.3V: C14.1, C15.1, C30.2, C45.1, C46.1, C47.1, C48.1, D19.2 (A), J2.6, R8.1, R39.1, R67.1, R70.1, R76.2, R86.1, R87.1, R96.1, TP1.1, U4.3 (VCC), U5.3 (3V3), U9.5 (VDDIO), U9.8 (VDD), U9.12 (CSB), U10.2 (CSB), U10.6 (VDDIO), U10.8 (VDD); also elsewhere on the board
+5V: D5.1 (K), IC1.6 (IN), LS1.1 (+); also elsewhere on the board
/5VSW: C25.2, D18.1 (K), IC1.1 (OUT); also elsewhere on the board
/BMS_AFE/ALERT: R15.1, R70.2, U5.22 (IO18); also elsewhere on the board
/BMS_AFE/CFETOFF: TP4.1, U5.10 (IO6); also elsewhere on the board
/BMS_AFE/DFETOFF: TP5.1, U5.11 (IO7); also elsewhere on the board
/BMS_AFE/RS_SHUT: TP6.1, U5.7 (IO3); also elsewhere on the board
/Button: D9.1 (K), R69.1, R76.1; also elsewhere on the board
/CANH: D6.1 (K), R36.1, U4.7 (CANH); also elsewhere on the board
/CANL: D2.1 (K), R36.2, U4.6 (CANL); also elsewhere on the board
/ESP32/5VSW_EN: IC1.4 (EN), R88.2, U5.18 (IO14), U5.26 (IO26)
/ESP32/5VSW_FLT: IC1.3 (~FAULT), R67.2, U5.25 (IO21)
/ESP32/BOOT: R39.2, SW2.1, U5.4 (IO0)
/ESP32/Button_uc: C41.2, R69.2, U5.16 (IO12)
/ESP32/Buzzer_PWM: R71.2, R72.1, U5.32 (IO36)
/ESP32/CAN_D: TP2.1, U4.1 (D), U5.8 (IO4)
/ESP32/CAN_EN: U4.5 (EN), U5.12 (IO8)
/ESP32/CAN_R: TP3.1, U4.4 (R), U5.9 (IO5)
/ESP32/CAN_RS: R63.1, U5.13 (IO9)
/ESP32/ESP_RST: C3.1, R8.2, SW1.2, U5.45 (EN)
/ESP32/GPIO1_uc: R52.2, U5.15 (IO11)
/ESP32/GPIO2_uc: R53.2, U5.17 (IO13)
/ESP32/IMU_INT1: U5.21 (IO17), U9.4 (INT1)
/ESP32/IO37: J2.8, U5.33 (IO37)
/ESP32/IO38: J2.3, U5.34 (IO38)
/ESP32/Key_uc: U5.14 (IO10); also elsewhere on the board
/ESP32/PI2C_SDA: J2.2, R86.2, TP12.1, U5.31 (IO35), U9.14 (SDx), U10.3 (SDI)
/ESP32/UART_RXD: J2.5, U5.40 (RXD0)
/ESP32/UART_TXD: J2.4, U5.39 (TXD0)
/ESP32/XTAL32_N: C56.2, U5.20 (IO16), Y1.2
/ESP32/XTAL32_P: C55.2, U5.19 (IO15), Y1.1
/GPIO1: D21.1 (K), R52.1, R96.2; also elsewhere on the board
/GPIO3: D16.1 (K), R89.2
/GPIO4: U5.36 (IO40)
/I2C_SCL: J2.10, TP8.1, U5.6 (IO2); also elsewhere on the board
/I2C_SDA: J2.9, TP9.1, U5.5 (IO1); also elsewhere on the board
/USB_D+: U5.23 (IO19), U5.24 (IO20); also elsewhere on the board
unnamed: D4.2 (A), U5.27 (IO47)
unnamed: D4.1 (K), R28.2
unnamed: D5.2 (A), LS1.2 (-), Q1.3 (D)
unnamed: D8.2 (A), U5.30 (IO48)
unnamed: D8.1 (K), R79.2
unnamed: D19.1 (K), R15.2
unnamed: IC1.2 (ILIM), R68.1
unnamed: Q1.1 (G), R71.1
unnamed: R63.2, U4.8 (Rs)
unnamed: R89.1, U5.35 (IO39)

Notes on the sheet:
IMU
HMI Input
5V output (400mA min)
Slew rate ca. 6V/us
Buzzer
CAN Transceiver
Enviromental sensor
ESP32 Main Controller
I2C address 0x68
I2C peripheral can be used from ULP RISCV
IO21 is last RTC IO
fres = 2.7kHz
I2C address 0x76
GPIO45/46 strapping pins
GPIO0 = Boot pin
Pinheader for debugging
Alternative Part for Buzzer: C161819

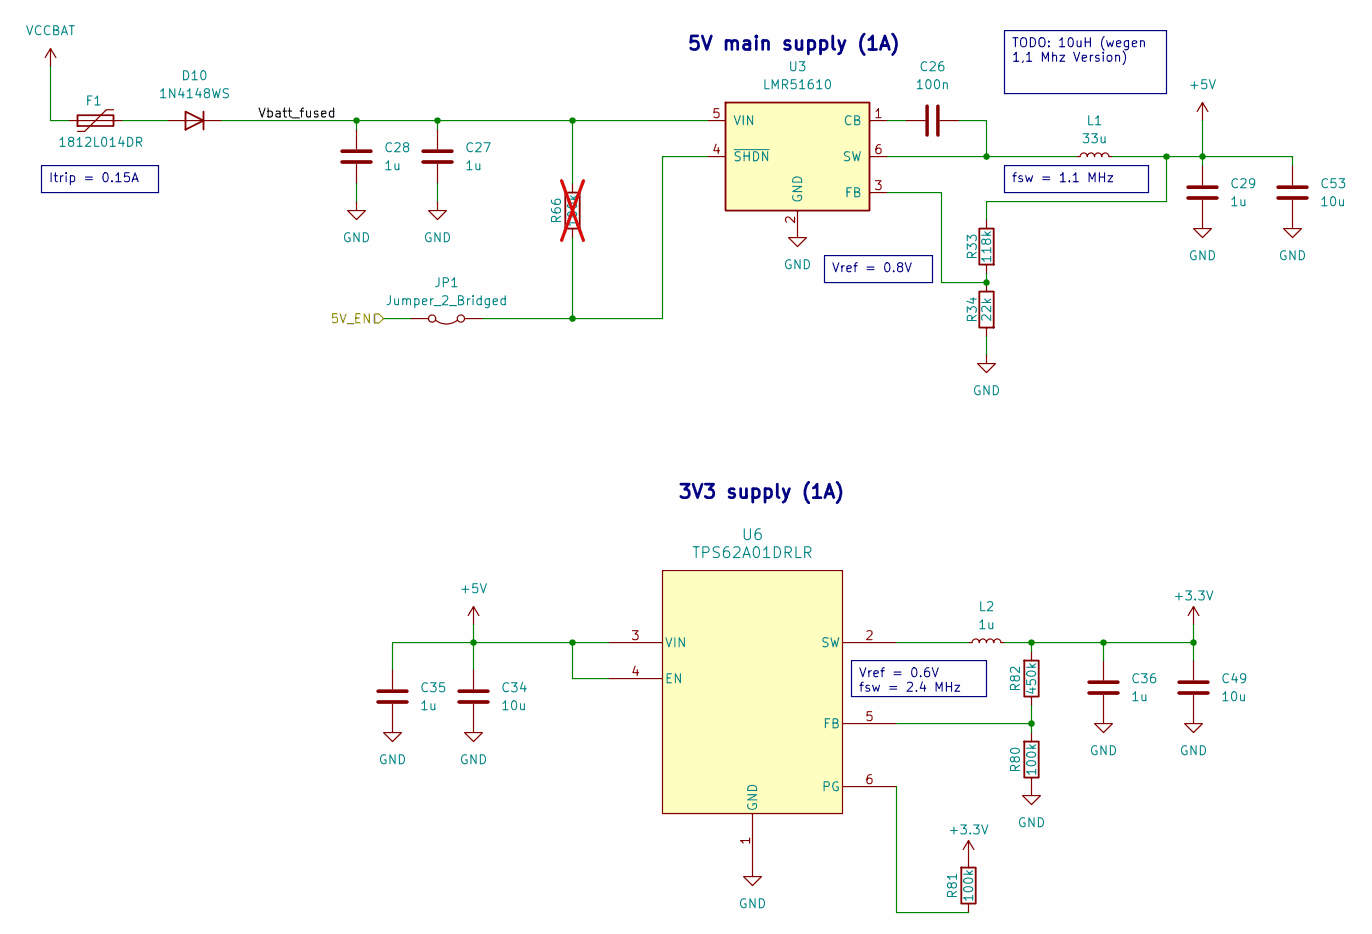
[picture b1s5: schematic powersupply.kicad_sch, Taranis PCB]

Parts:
C26: 100n; C_0402_1005Metric; MPN C307331
C27, C28: 1u; C_1206_3216Metric; MPN C13832
C29, C35, C36: 1u; C_0402_1005Metric; MPN C52923
C34, C49, C53: 10u; C_0402_1005Metric; MPN C15525
D10: 1N4148WS; D_SOD-323; MPN C2128
F1: 1812L014DR; R_1812_4532Metric; MPN C151166
JP1: Jumper_2_Bridged; SolderJumper-2_P1.3mm_Bridged_RoundedPad1.0x1.5mm
L1: 33u; L_Sunlord_SWPA6045S; MPN C83451
L2: 1u; L_1008_2520Metric; MPN C435392
R33: 118k; R_0402_1005Metric; MPN C25748
R34: 22k; R_0402_1005Metric; MPN C25768
R66: 100k; R_0402_1005Metric; MPN C25741; not fitted
R80, R81: 100k; R_0402_1005Metric; MPN C25741
R82: 450k; R_0402_1005Metric; MPN C5159688
U3: LMR51610; SOT-23-6; MPN C33545953
U6: TPS62A01DRLR; SOT6_DRL_TEX; MPN C5157937

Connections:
+1V8: JP1.2 (B); also elsewhere on the board
+3.3V: C36.2, C49.2, L2.2, R81.2, R82.2; also elsewhere on the board
+5V: C29.2, C34.2, C35.2, C53.2, L1.2, R33.1, U6.3 (VIN), U6.4 (EN); also elsewhere on the board
/Power Supply/Vbatt_fused: C27.2, C28.2, D10.1 (K), R66.2, U3.5 (VIN)
unnamed: D10.2 (A), F1.2
unnamed: JP1.1 (A), R66.1, U3.4 (~SHDN)
unnamed: C26.1, U3.1 (CB)
unnamed: R33.2, R34.1, U3.3 (FB)
unnamed: C26.2, L1.1, U3.6 (SW)
unnamed: R80.2, R82.1, U6.5 (FB)
unnamed: R81.1, U6.6 (PG)
unnamed: L2.1, U6.2 (SW)
VCCBAT: F1.1; also elsewhere on the board

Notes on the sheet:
5V main supply (1A)
3V3 supply (1A)
Vref = 0.6V fsw = 2.4 MHz
Itrip = 0.15A
fsw = 1.1 MHz
TODO: 10uH (wegen 1,1 Mhz Version)
Vref = 0.8V

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

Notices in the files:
ESP32.kicad_sch:
Taranis PCB © 2025 by Stefan Kraus is licensed under CERN-OHL-P-2.0
